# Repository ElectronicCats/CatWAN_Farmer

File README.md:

# CatWAN Farmer by Electronic Cats

CatWAN Farmer, a grower's water saving project

Monitoring soil moisture at different depths to determine when to irrigate, and - more importantly - how much water is needed. Save 25%!

## Main characteristics

- Provide low cost, easy to build, and rugged components for optimizing agricultural irrigation.
- DIY calibrated gypsum soil moisture sensors (Watermark SS200 is also supported).
- Hand held sensor reader (soil moisture, soil/water salinity, water pressure).
- Solar powered remote sensor platform.
- 4 electrically separated inputs for soil moisture sensors.
- LoRa module for long range (6 miles).
- temperature/humidity sensors.
- Solar battery charger.
- Real time clock for sleep mode power saving and precise irrigation timing.
- Gateway to connect multiple LoRa end nodes to the Internet.
- Supports packet mode LoRa® (package mode) or LoRaWAN ™ Class A, B and C.
- Compatible with Beelan, The Things Network and other LoRaWAN networks.
- Easy reprogramming compatible with Arduino and Circuit Python.

## Specifications

- 32-bit ARM Cortex-M0+ processor with 256KB flash, 32KB SRAM, and an operating speed of up to 48MHz. 
- Connectivity: USB 2.1.
- Vin: 4.2V-6.0V for charger - otherwise 3.5V-6.0V
- VBATT: 3.7V Lipo
- VCC: 600mA @3.3V
- Receiver Sensitivity: down to -146 dBm.
- TX Power: adjustable up to +18.5 dBm.
- Range: up to 15 km coverage in suburban and up to 5 km coverage.
- Watermark SS200 soil water tension sensor (4 x).
- Capacitive (FDR) volumetric soil moisture sensors (3x).
- Temperature and humidity.
- Compatible LoRa 915 and 868 Mhz.

## LICENSE

Hardware released under an CERN Open Hardware Licence v1.2. See the LICENSE_HARDWARE file for more information.

Designed by Electronic Cats.

Electronic Cats is a registered trademark, please do not use if you sell these PCBs.

Electronic Cats invests time and resources providing this open source design, please support Electronic Cats and open-source hardware by purchasing products from Electronic Cats!

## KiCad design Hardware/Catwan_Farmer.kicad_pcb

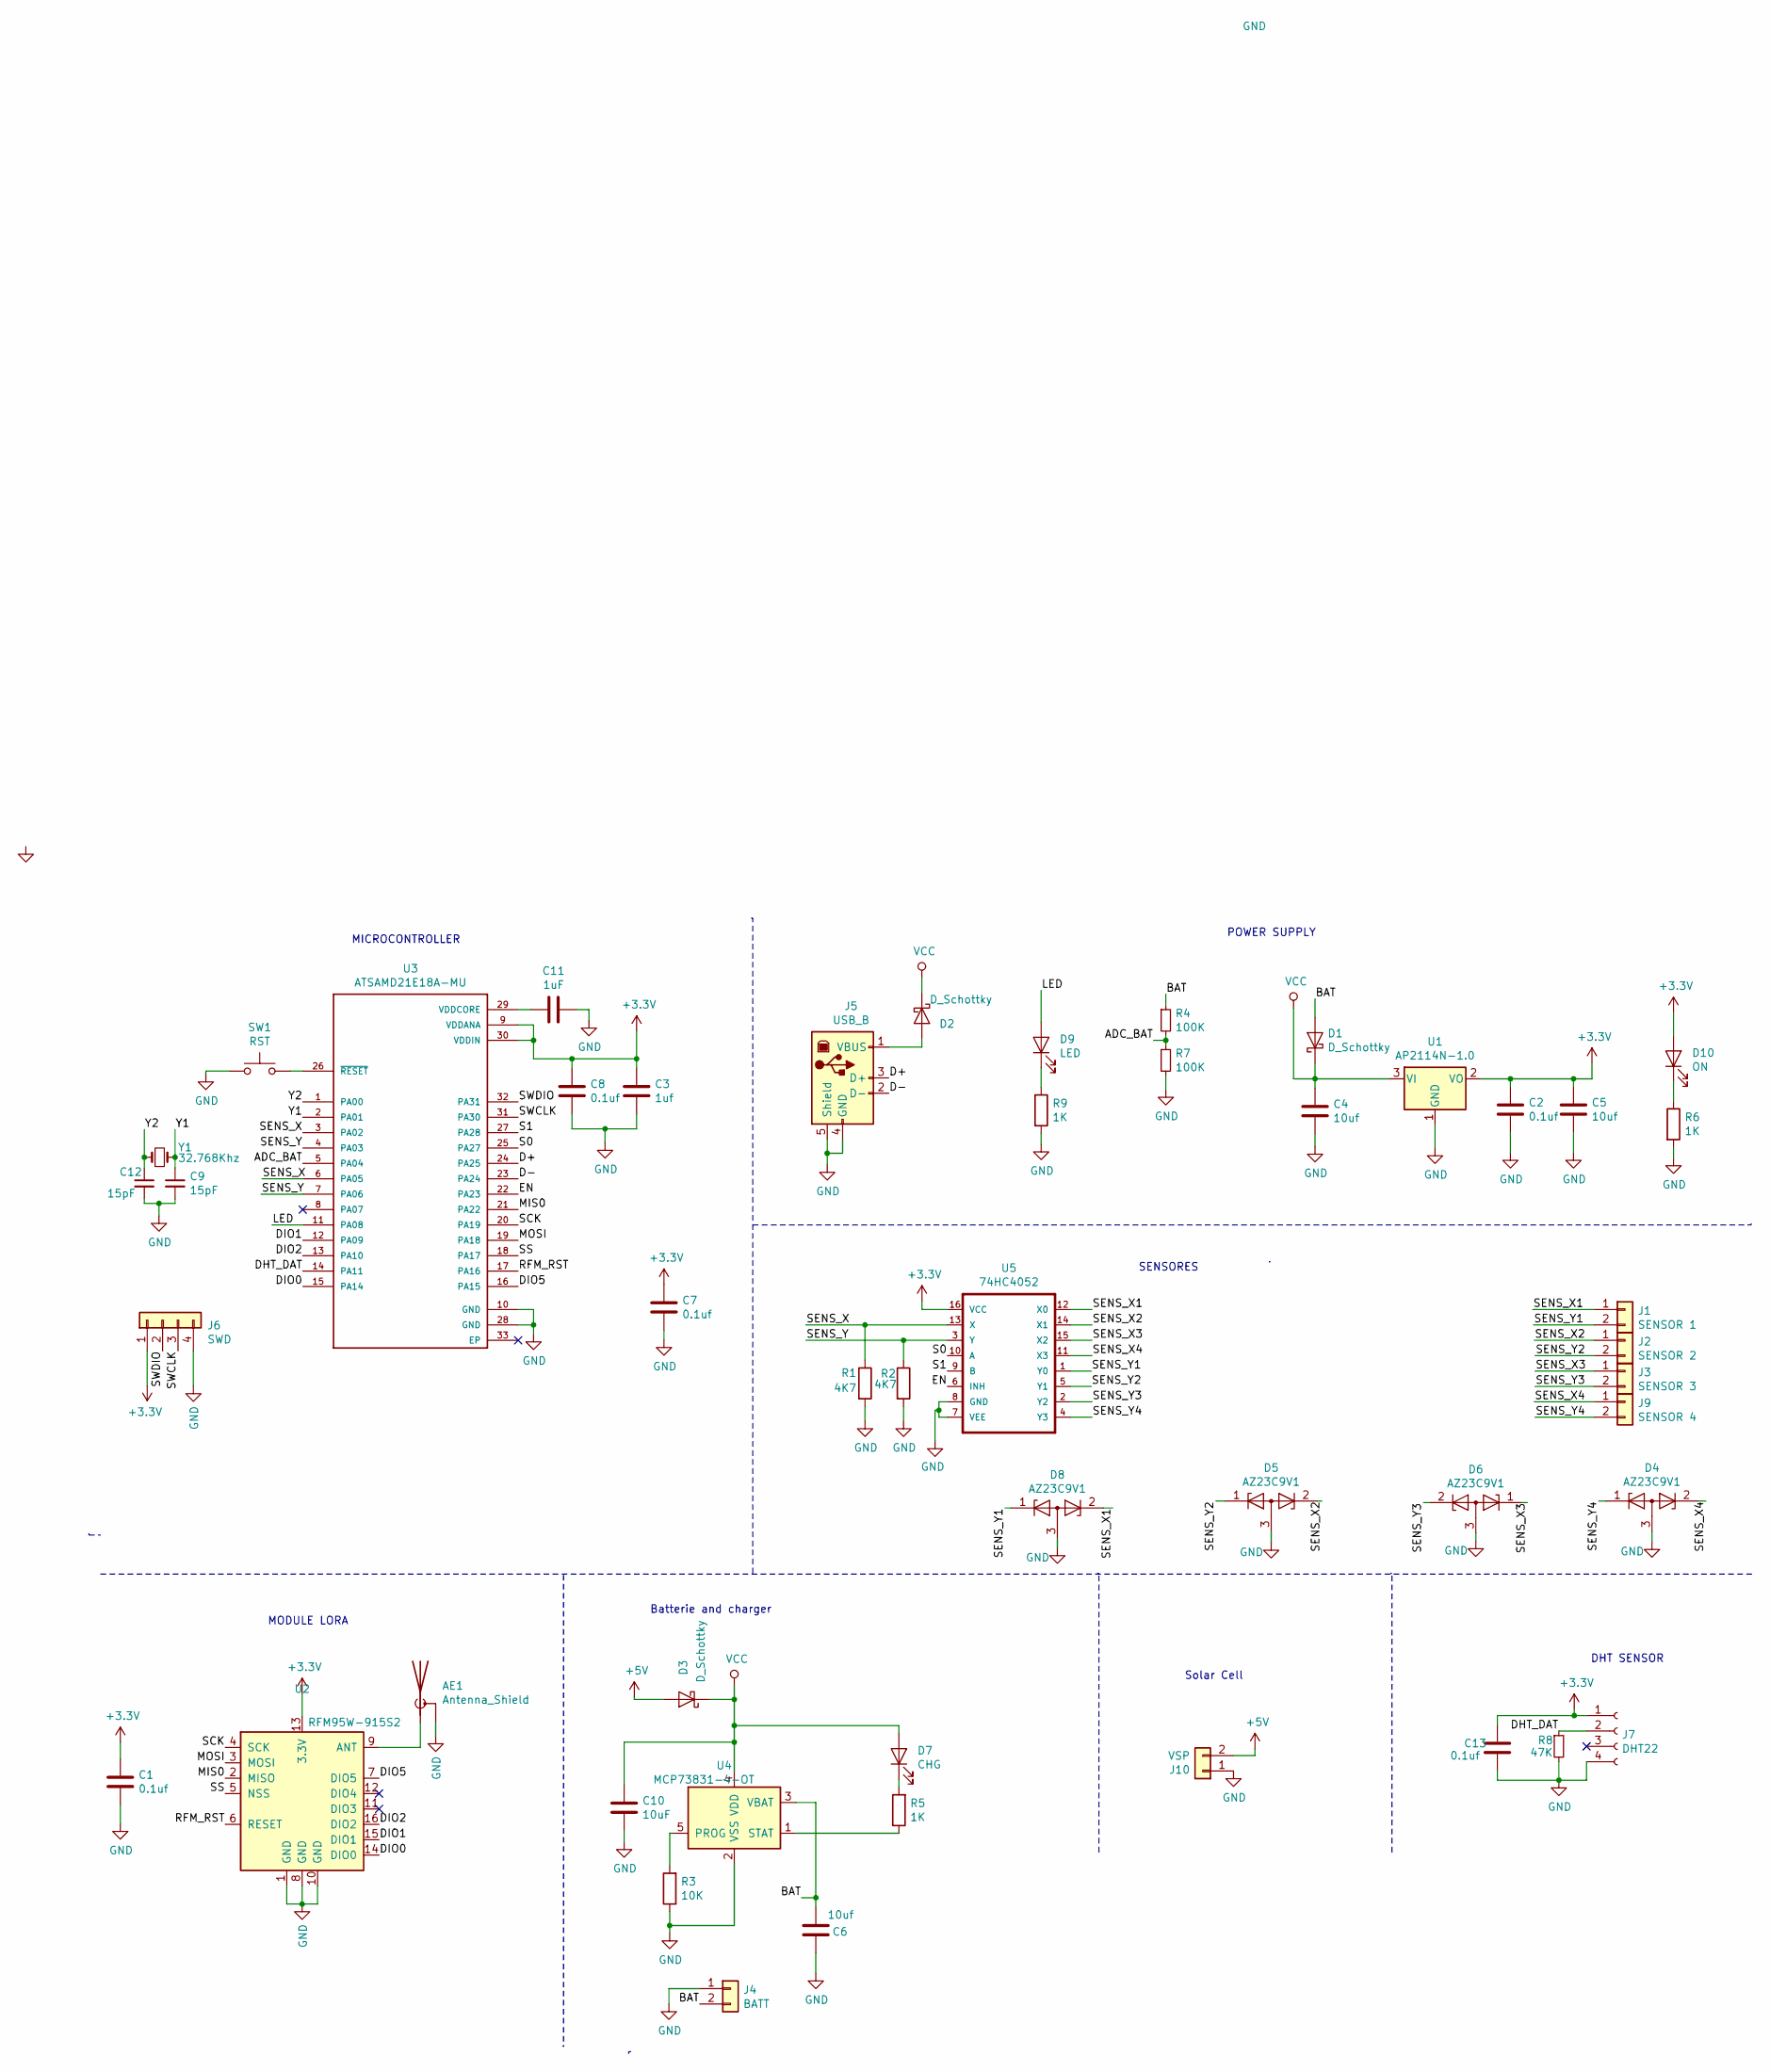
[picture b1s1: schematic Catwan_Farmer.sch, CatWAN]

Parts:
AE1: Antenna_Shield; AMPHENOL_901-144
C1, C2, C7, C8, C13: 0.1uf; C_0805_2012Metric_Pad1.15x1.40mm_HandSolder
C3: 1uf; C_0805_2012Metric_Pad1.15x1.40mm_HandSolder
C4, C5, C6: 10uf; C_0805_2012Metric_Pad1.15x1.40mm_HandSolder
C9, C12: 15pF; C_0805_2012Metric_Pad1.15x1.40mm_HandSolder
C10: 10uF; C_0805_2012Metric_Pad1.15x1.40mm_HandSolder
C11: 1uF; C_0805_2012Metric_Pad1.15x1.40mm_HandSolder
D1, D2, D3: D_Schottky; D_SOD-123
D4, D5, D6, D8: AZ23C9V1; SOT-23
D7: CHG; LED_0805_2012Metric_Pad1.15x1.40mm_HandSolder
D9: LED; LED_0805_2012Metric_Pad1.15x1.40mm_HandSolder
D10: ON; LED_0805_2012Metric_Pad1.15x1.40mm_HandSolder
J1: SENSOR 1; TerminalBlock_Phoenix_PT-1,5-2-3.5-H_1x02_P3.50mm_Horizontal
J2: SENSOR 2; TerminalBlock_Phoenix_PT-1,5-2-3.5-H_1x02_P3.50mm_Horizontal
J3: SENSOR 3; TerminalBlock_Phoenix_PT-1,5-2-3.5-H_1x02_P3.50mm_Horizontal
J4: BATT; TerminalBlock_Phoenix_PT-1,5-2-3.5-H_1x02_P3.50mm_Horizontal
J5: USB_B; U254051N4BH806
J6: SWD; PinHeader_1x04_P2.54mm_Vertical
J7: DHT22; PinHeader_1x04_P2.54mm_Vertical
J9: SENSOR 4; TerminalBlock_Phoenix_PT-1,5-2-3.5-H_1x02_P3.50mm_Horizontal
J10: VSP; TerminalBlock_Phoenix_PT-1,5-2-3.5-H_1x02_P3.50mm_Horizontal
R1, R2: 4K7; R_0805_2012Metric_Pad1.15x1.40mm_HandSolder
R3: 10K; R_0805_2012Metric_Pad1.15x1.40mm_HandSolder
R4, R7: 100K; R_0805_2012Metric_Pad1.15x1.40mm_HandSolder
R5, R6, R9: 1K; R_0805_2012Metric_Pad1.15x1.40mm_HandSolder
R8: 47K; R_0805_2012Metric_Pad1.15x1.40mm_HandSolder
SW1: RST; SW_SPST_SKQG_WithStem
U1: AP2114N-1.0; SOT-223-3_TabPin2
U2: RFM95W-915S2; HOPERF_RFM9XW_SMD
U3: ATSAMD21E18A-MU; TQFP-32_7x7mm_P0.8mm
U4: MCP73831-4-OT; SOT-23-5
U5: 74HC4052; SOIC-16_3.9x9.9mm_P1.27mm
Y1: 32.768Khz; Crystal_SMD_MicroCrystal_CC7V-T1A-2Pin_3.2x1.5mm_HandSolder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

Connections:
+3V3: C1.1, C2.1, C3.1, C5.1, C7.1, C8.1, C13.1, D10.2 (A), J6.1, J7.1, U1.2 (VO), U2.13 (3.3V), U3.9 (VDDANA), U3.30 (VDDIN), U5.16 (VCC)
+5V: D3.2 (A), J10.2
/ADC_BAT: R4.2, R7.1, U3.5 (PA04)
/BAT: C6.2, D1.2 (A), J4.2, R4.1, U4.3 (VBAT)
/D+: J5.3 (D+), U3.24 (PA25)
/D-: J5.2 (D-), U3.23 (PA24)
/DHT_DAT: J7.2, R8.1, U3.14 (PA11)
/DIO0: U2.14 (DIO0), U3.15 (PA14)
/DIO1: U2.15 (DIO1), U3.12 (PA09)
/DIO2: U2.16 (DIO2), U3.13 (PA10)
/DIO5: U2.7 (DIO5), U3.16 (PA15)
/EN: U3.22 (PA23), U5.6 (INH)
/LED: D9.2 (A), U3.11 (PA08)
/MIS0: U2.2 (MISO), U3.21 (PA22)
/MOSI: U2.3 (MOSI), U3.19 (PA18)
/RFM_RST: U2.6 (RESET), U3.17 (PA16)
/S0: U3.25 (PA27), U5.10 (A)
/S1: U3.27 (PA28), U5.9 (B)
/SCK: U2.4 (SCK), U3.20 (PA19)
/SENS_X: R1.1, U3.3 (PA02), U3.6 (PA05), U5.13 (X)
/SENS_X1: D8.2 (K), J1.1, U5.12 (X0)
/SENS_X2: D5.2 (K), J2.1, U5.14 (X1)
/SENS_X3: D6.1 (K), J3.1, U5.15 (X2)
/SENS_X4: D4.2 (K), J9.1, U5.11 (X3)
/SENS_Y: R2.1, U3.4 (PA03), U3.7 (PA06), U5.3 (Y)
/SENS_Y1: D8.1 (K), J1.2, U5.1 (Y0)
/SENS_Y2: D5.1 (K), J2.2, U5.5 (Y1)
/SENS_Y3: D6.2 (K), J3.2, U5.2 (Y2)
/SENS_Y4: D4.1 (K), J9.2, U5.4 (Y3)
/SS: U2.5 (NSS), U3.18 (PA17)
/SWCLK: J6.3, U3.31 (PA30)
/SWDIO: J6.2, U3.32 (PA31)
/Y1: C9.1, U3.2 (PA01), Y1.2
/Y2: C12.1, U3.1 (PA00), Y1.1
GND: AE1.2 (Shield), C1.2, C2.2, C3.2, C4.2, C5.2, C6.1, C7.2, C8.2, C9.2, C10.2, C11.1, C12.2, C13.2, D4.3 (A), D5.3 (A), D6.3 (A), D8.3 (A), J4.1, J5.4 (GND), J5.5 (Shield), J6.4, J7.4, J10.1, R1.2, R2.2, R3.1, R6.2, R7.2, R8.2, R9.2, SW1.1, U1.1 (GND), U2.1 (GND), U2.8 (GND), U2.10 (GND), U3.10 (GND), U3.28 (GND), U4.2 (VSS), U5.7 (VEE), U5.8 (GND)
unnamed: AE1.1 (A), U2.9 (ANT)
unnamed: C11.2, U3.29 (VDDCORE)
unnamed: D2.2 (A), J5.1 (VBUS)
unnamed: D7.1 (K), R5.2
unnamed: D9.1 (K), R9.1
unnamed: D10.1 (K), R6.1
unnamed: R3.2, U4.5 (PROG)
unnamed: R5.1, U4.1 (STAT)
unnamed: SW1.2, U3.26 (~RESET~)
VCC: C4.1, C10.1, D1.1 (K), D2.1 (K), D3.1 (K), D7.2 (A), U1.3 (VI), U4.4 (VDD)

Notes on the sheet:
MICROCONTROLLER
POWER SUPPLY
MODULE LORA
SENSORES
Solar Cell
DHT SENSOR
Batterie and charger

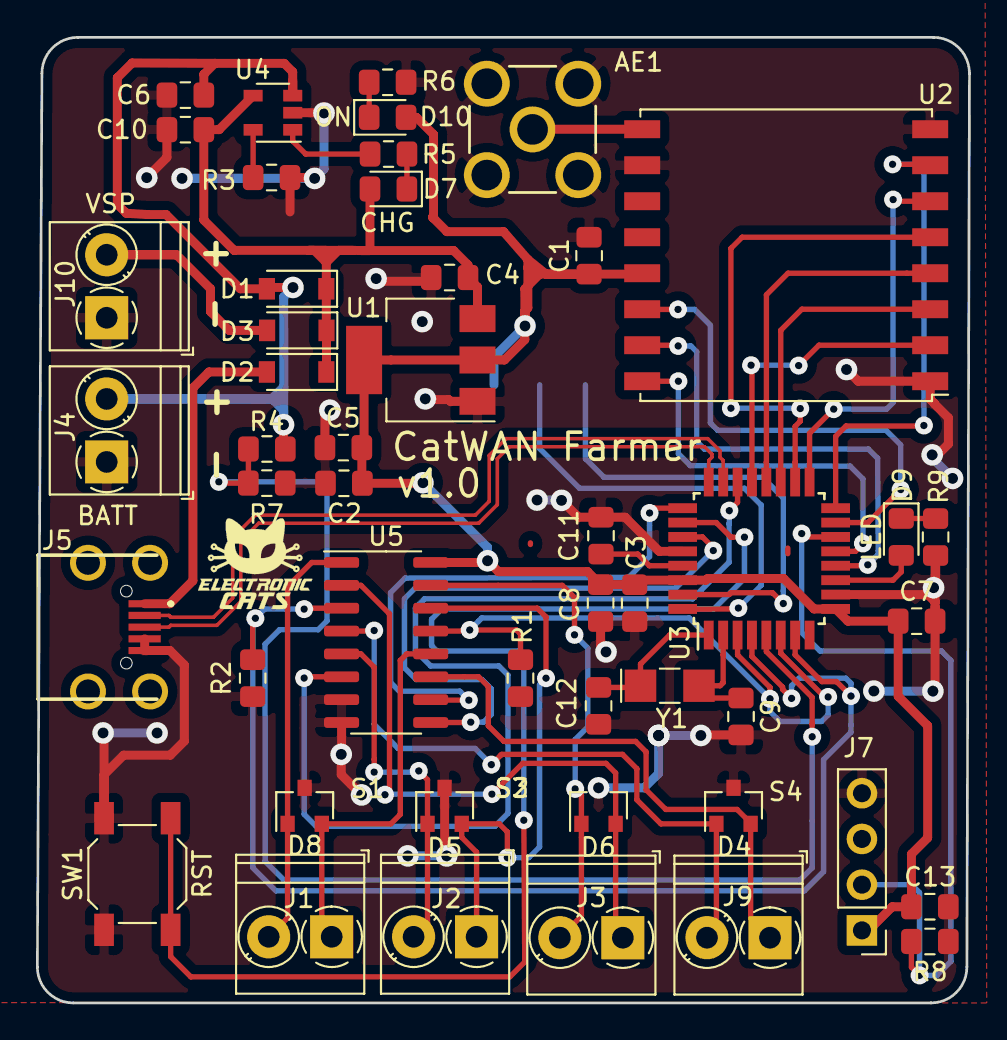
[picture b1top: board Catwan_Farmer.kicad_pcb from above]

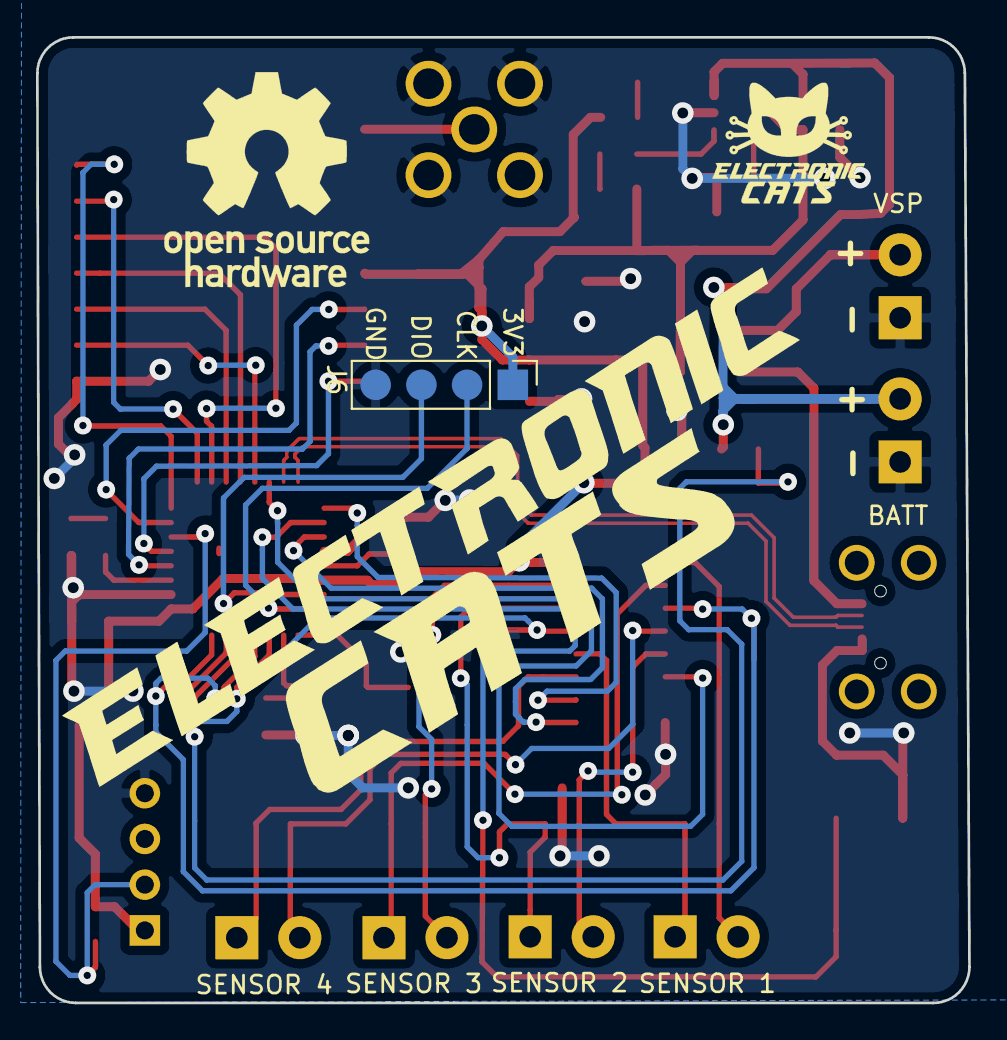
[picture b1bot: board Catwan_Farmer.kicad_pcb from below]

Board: 2 copper layers, 51.8 x 53.6 mm, 50 parts (2 on the bottom side), 45 nets.

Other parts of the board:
svg2mod: electronic; titule_electronic_med

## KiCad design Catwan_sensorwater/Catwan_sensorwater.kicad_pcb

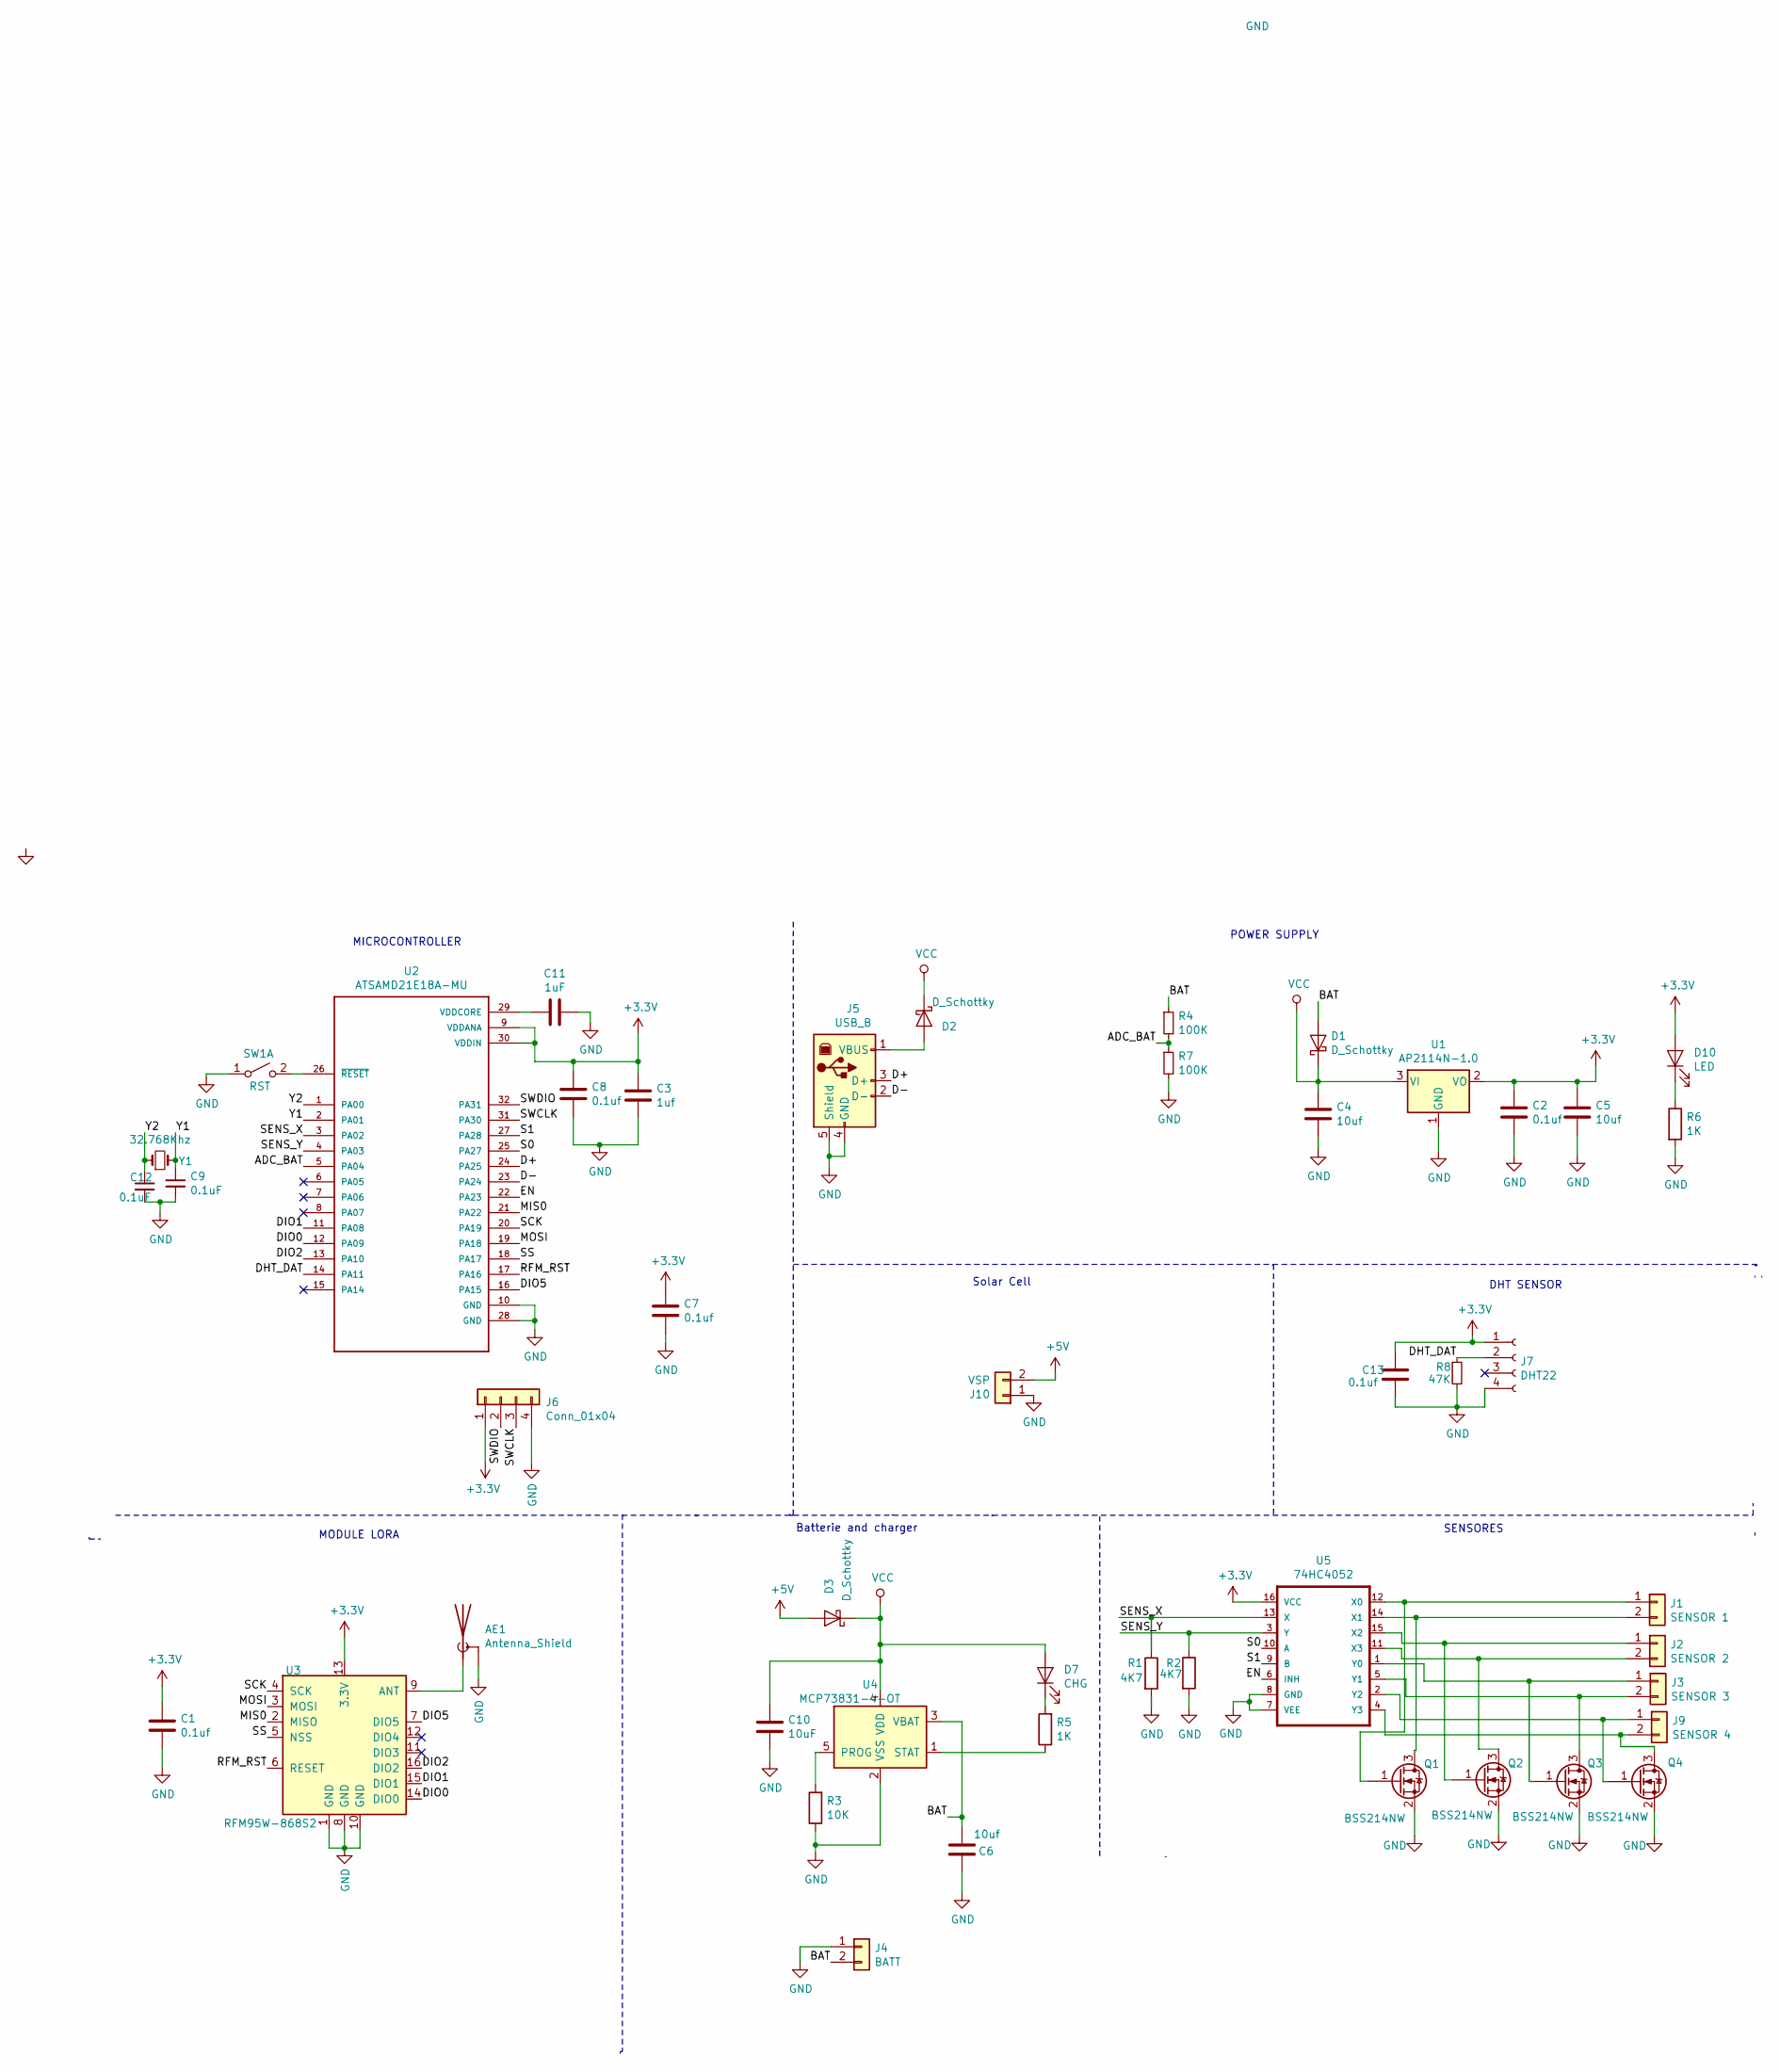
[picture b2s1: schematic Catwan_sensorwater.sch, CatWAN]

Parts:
AE1: Antenna_Shield; AMPHENOL_901-144
C1, C2, C7, C8, C13: 0.1uf; C_0805_2012Metric_Pad1.15x1.40mm_HandSolder
C3: 1uf; C_0805_2012Metric_Pad1.15x1.40mm_HandSolder
C4, C5, C6: 10uf; C_0805_2012Metric_Pad1.15x1.40mm_HandSolder
C9, C12: 0.1uF; C_0805_2012Metric_Pad1.15x1.40mm_HandSolder
C10: 10uF; C_0805_2012Metric_Pad1.15x1.40mm_HandSolder
C11: 1uF; C_0805_2012Metric_Pad1.15x1.40mm_HandSolder
D1, D2, D3: D_Schottky; D_SOD-123
D7: CHG; LED_0805_2012Metric_Pad1.15x1.40mm_HandSolder
D10: LED; LED_0805_2012Metric_Pad1.15x1.40mm_HandSolder
J1: SENSOR 1; TerminalBlock_Phoenix_PT-1,5-2-3.5-H_1x02_P3.50mm_Horizontal
J2: SENSOR 2; TerminalBlock_Phoenix_PT-1,5-2-3.5-H_1x02_P3.50mm_Horizontal
J3: SENSOR 3; TerminalBlock_Phoenix_PT-1,5-2-3.5-H_1x02_P3.50mm_Horizontal
J4: BATT; TerminalBlock_Phoenix_PT-1,5-2-3.5-H_1x02_P3.50mm_Horizontal
J5: USB_B; USB_Micro-B_Wuerth_629105150521
J6: Conn_01x04; PinHeader_1x04_P2.54mm_Vertical
J7: DHT22; PinHeader_1x04_P2.54mm_Vertical
J9: SENSOR 4; TerminalBlock_Phoenix_PT-1,5-2-3.5-H_1x02_P3.50mm_Horizontal
J10: VSP; TerminalBlock_Phoenix_PT-1,5-2-3.5-H_1x02_P3.50mm_Horizontal
Q1, Q2, Q3, Q4: BSS214NW; SOT-23
R1, R2: 4K7; R_0805_2012Metric_Pad1.15x1.40mm_HandSolder
R3: 10K; R_0805_2012Metric_Pad1.15x1.40mm_HandSolder
R4, R7: 100K; R_0805_2012Metric_Pad1.15x1.40mm_HandSolder
R5, R6: 1K; R_0805_2012Metric_Pad1.15x1.40mm_HandSolder
R8: 47K; R_0805_2012Metric_Pad1.15x1.40mm_HandSolder
SW1: RST; SW_SPST_TL3342
U1: AP2114N-1.0; SOT-223-3_TabPin2
U2: ATSAMD21E18A-MU; TQFP-32_7x7mm_P0.8mm
U3: RFM95W-868S2; RFM95W
U4: MCP73831-4-OT; SOT-23-5
U5: 74HC4052; SOIC-16_3.9x9.9mm_P1.27mm
Y1: 32.768Khz; Crystal_AT310_d3.0mm_l10.0mm_Vertical

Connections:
+3V3: C1.1, C2.1, C3.1, C5.1, C7.1, C8.1, C13.1, D10.2 (A), J6.1, J7.1, U1.2 (VO), U2.9 (VDDANA), U2.30 (VDDIN), U3.13 (3.3V), U5.16 (VCC)
+5V: D3.2 (A), J10.2
/ADC_BAT: R4.2, R7.1, U2.5 (PA04)
/BAT: C6.2, D1.2 (A), J4.2, R4.1, U4.3 (VBAT)
/D+: J5.3 (D+), U2.24 (PA25)
/D-: J5.2 (D-), U2.23 (PA24)
/DHT_DAT: J7.2, R8.1, U2.14 (PA11)
/DIO2: U2.13 (PA10), U3.16 (DIO2)
/DIO5: U2.16 (PA15), U3.7 (DIO5)
/EN: U2.22 (PA23), U5.6 (INH)
/MIS0: U2.21 (PA22), U3.2 (MISO)
/MOSI: U2.19 (PA18), U3.3 (MOSI)
/RFM_RST: U2.17 (PA16), U3.6 (RESET)
/S0: U2.25 (PA27), U5.10 (A)
/S1: U2.27 (PA28), U5.9 (B)
/SCK: U2.20 (PA19), U3.4 (SCK)
/SENS_X: R1.1, U2.3 (PA02), U5.13 (X)
/SENS_Y: R2.1, U2.4 (PA03), U5.3 (Y)
/SS: U2.18 (PA17), U3.5 (NSS)
/SWCLK: J6.3, U2.31 (PA30)
/SWDIO: J6.2, U2.32 (PA31)
/Y1: C9.1, U2.2 (PA01), Y1.2
/Y2: C12.1, U2.1 (PA00), Y1.1
GND: AE1.2 (Shield), C1.2, C2.2, C3.2, C4.2, C5.2, C6.1, C7.2, C8.2, C9.2, C10.2, C11.1, C12.2, C13.2, J4.1, J5.4 (GND), J5.5 (Shield), J6.4, J7.4, J10.1, Q1.2 (S), Q2.2 (S), Q3.2 (S), Q4.2 (S), R1.2, R2.2, R3.1, R6.2, R7.2, R8.2, SW1.1 (A), U1.1 (GND), U2.10 (GND), U2.28 (GND), U3.1 (GND), U3.8 (GND), U3.10 (GND), U4.2 (VSS), U5.7 (VEE), U5.8 (GND)
unnamed: AE1.1 (A), U3.9 (ANT)
unnamed: C11.2, U2.29 (VDDCORE)
unnamed: D2.2 (A), J5.1 (VBUS)
unnamed: D7.1 (K), R5.2
unnamed: D10.1 (K), R6.1
unnamed: J1.1, Q1.1 (G), U5.12 (X0)
unnamed: J1.2, Q1.3 (D), U5.14 (X1)
unnamed: J2.1, Q2.1 (G), U5.15 (X2)
unnamed: J2.2, Q2.3 (D), U5.11 (X3)
unnamed: J3.1, Q3.1 (G), U5.1 (Y0)
unnamed: J3.2, Q3.3 (D), U5.5 (Y1)
unnamed: J9.1, Q4.1 (G), U5.2 (Y2)
unnamed: J9.2, Q4.3 (D), U5.4 (Y3)
unnamed: R3.2, U4.5 (PROG)
unnamed: R5.1, U4.1 (STAT)
unnamed: SW1.2 (B), U2.26 (~RESET~)
VCC: C4.1, C10.1, D1.1 (K), D2.1 (K), D3.1 (K), D7.2 (A), U1.3 (VI), U4.4 (VDD)

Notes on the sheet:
MICROCONTROLLER
POWER SUPPLY
MODULE LORA
SENSORES
Solar Cell
DHT SENSOR
Batterie and charger

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
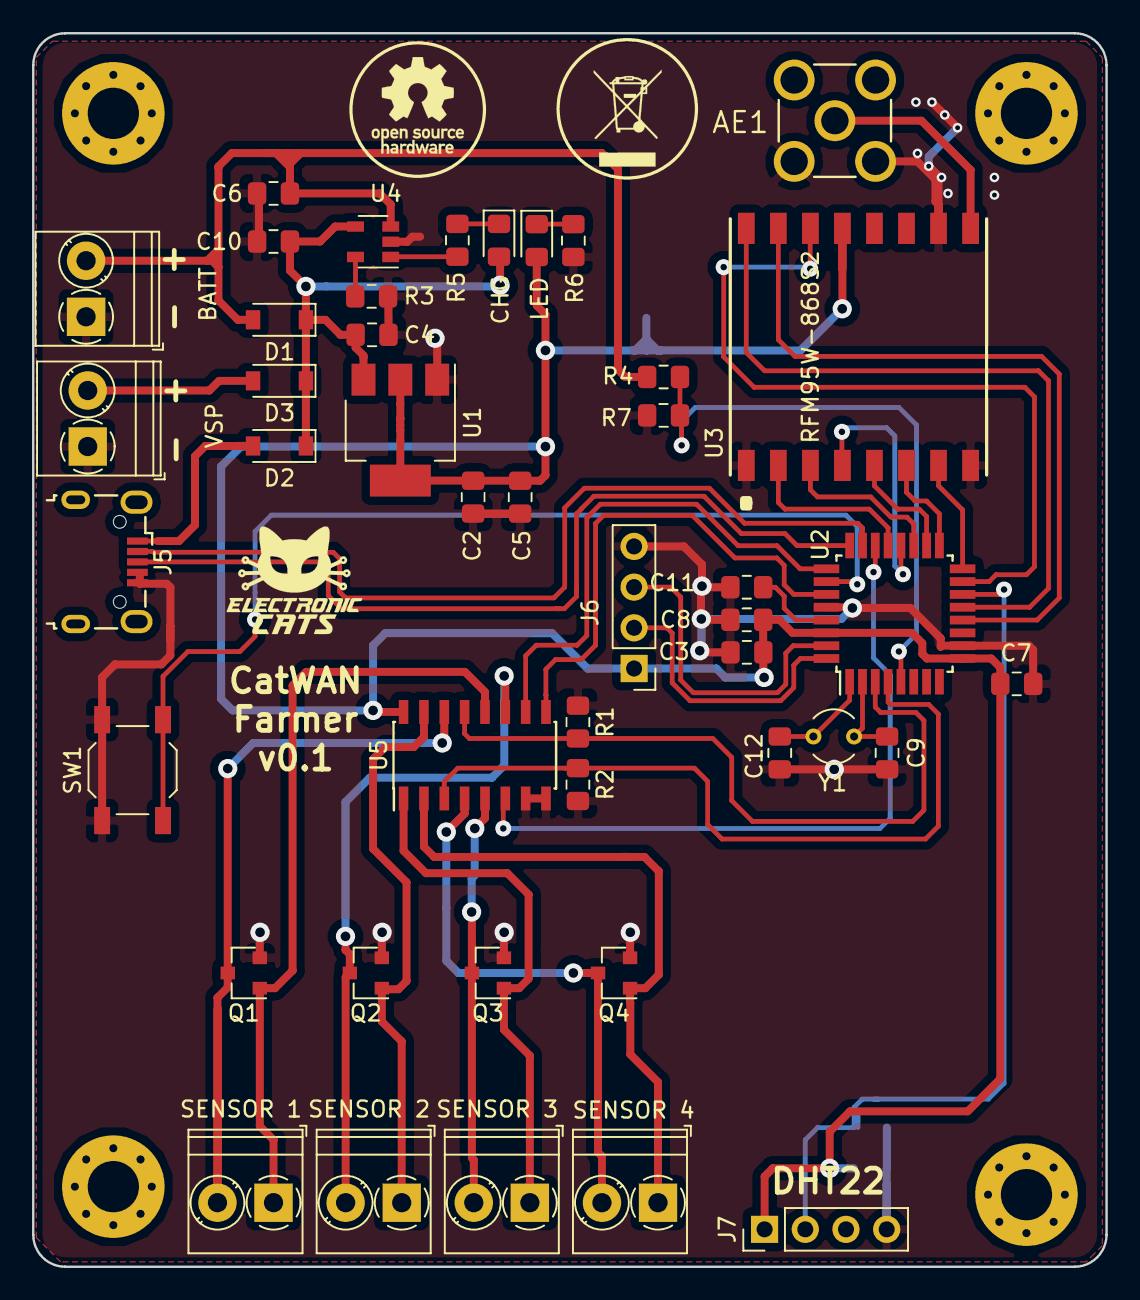
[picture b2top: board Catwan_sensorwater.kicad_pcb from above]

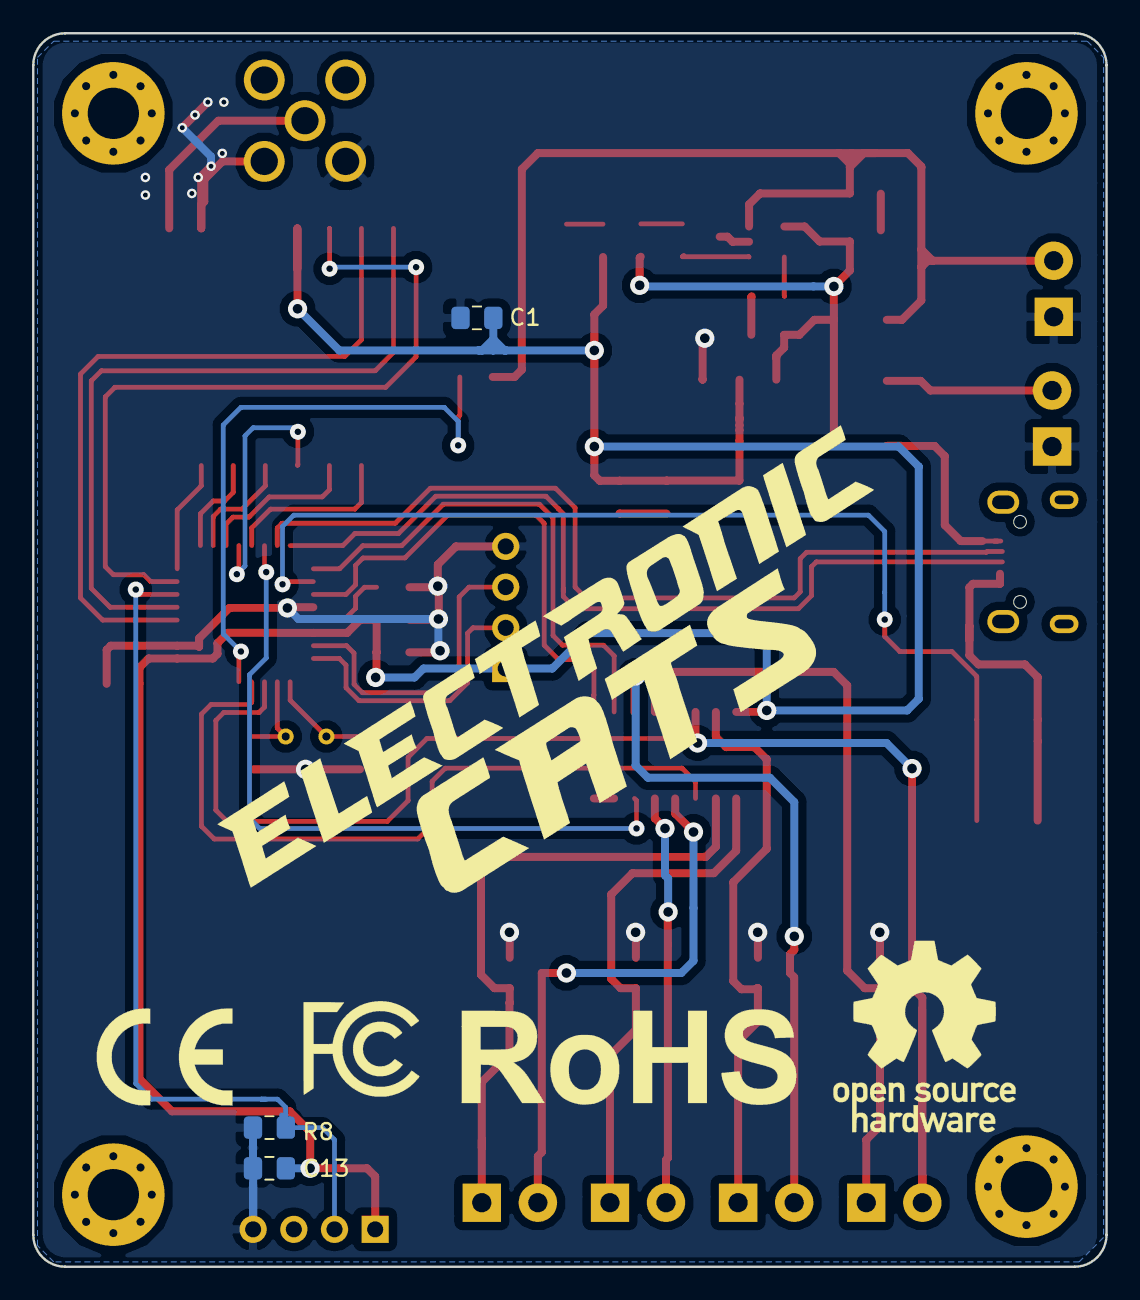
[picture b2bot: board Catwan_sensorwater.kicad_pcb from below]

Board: 2 copper layers, 67.0 x 77.0 mm, 48 parts (4 on the bottom side), 43 nets.

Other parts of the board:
svg2mod: electronic; titule_electronic_med

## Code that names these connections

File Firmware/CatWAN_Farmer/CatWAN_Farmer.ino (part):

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// Setting up format for reading 4 soil sensors
#define NUM_READS 10   // Number of sensor reads for filtering

#define SENS_X 5
#define SENS_Y 6
#define ENABLE 23
#define S0 27
#define S1 28
#define ADC_BAT A2
#define DHTPIN 11
#define DHTTYPE DHT22

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const sRFM_pins RFM_pins = {
  .CS = 20,
  .RST = 9,
  .DIO0 = 0,
  .DIO1 = 1,
  .DIO2 = 2,
  .DIO5 = 15,
};
*/

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  // setting up the sensor interface
  // initialize digital pins D5, D6 as an high impedance input.
  // Pin 5,6 are f846r driving the soil moisture sensor
  pinMode(SENS_X, INPUT); // SENS_X
  pinMode(SENS_Y, INPUT); // SENS_Y
  // Pin 7 is for enabling Mux switches
  pinMode(ENABLE, OUTPUT); //ENABLE
  // Pin 8,9 are for selecting sensor 1-4
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  for (i = 0; i < NUM_READS; i++)
  {

    pinMode(SENS_X, OUTPUT);
    digitalWrite(SENS_X, HIGH);
    delayMicroseconds(25);
    sensorVoltage = analogRead(A1);   // read the sensor voltage
    supplyVoltage = analogRead(A0);   // read the supply voltage
    delayMicroseconds(25);
    digitalWrite(SENS_X, LOW);
    pinMode(SENS_X, INPUT);
    delay(100);
    long resistance = (knownResistor * (supplyVoltage - sensorVoltage ) / sensorVoltage) - zeroCalibration ;
    addReading(resistance);
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#endif
    delay(1);

    pinMode(SENS_Y, OUTPUT);
    digitalWrite(SENS_Y, LOW);
    digitalWrite(SENS_Y, HIGH);
    delayMicroseconds(25);
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    supplyVoltage = analogRead(A1);   // read the supply voltage
    delayMicroseconds(25);
    digitalWrite(SENS_Y, LOW);
    pinMode(SENS_Y, INPUT);

    resistance = (knownResistor * (supplyVoltage - sensorVoltage ) / sensorVoltage) - zeroCalibration ;
    delay(100);
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
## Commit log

2018-09-24 Project_kiCad
2018-09-26 Regulador
    3.3V
2018-09-29 Agregue ATSAMD Y LORA
2018-10-01 Read sensor humidity arduino 1
2018-10-02 SENSORES, MULTIPLEXOR
2018-10-03 Multiplexor casi listo.
2018-10-03 asignación huellas
2018-10-04 Read voltaje divisor SAMD21
2018-10-04 Read MUX A0 A1
2018-10-09 batería agregada.
2018-10-10 huellas
    Cambios
2018-10-25 add s0 s1 ans enable in multiplexer
2018-10-25 Edit ATSAMD separate pin 10 and 28 an no connected
2018-10-25 Capacitor VCC SAMD
2018-10-26 Edit connections
2018-10-26 Adjust of regulator
2018-10-30 Connector ID
2018-10-30 Fix
    Serial SWD
2018-10-31 Pin modificado
    separados
2018-10-31 Footprints
2018-10-31 Auto stash before merge of "master" and "origin/master"
    Change zener for MOSFET
2018-10-31 add 3.3V to mux
2018-10-31 Annotate no. MOSFET
2018-10-31 ADD HUMIDITY SENSOR
2018-11-01 Add 4 sensor
2018-11-07 snapshot v0.3
    Update source to VCC, and check ERC
2018-11-07 remove resistence for DHT22
2018-11-12 Capacitor .1
2018-11-13 Changes connections and error
2018-11-13 Connections and error
2018-11-13 Finished schematic
2018-11-13 schematic modified
2018-11-13 Netlist
2018-11-13 Mover carpeta software
2018-11-13 change pines j6
2018-11-13 Change j7
2018-11-13 Inicio PCB
2018-11-16 acomodo
2018-11-17 Acomodo segunda parte
2018-11-20 Acomodo componentes
2018-11-21 Rooteo
2018-11-22 Segunda parte
2018-11-22 distribution devices
2018-11-22 Change diodes
2018-11-22 clear schematic
2018-11-23 change pcb
2018-11-23 components back to the front
2018-11-23 diode shottkie and regulator packege
2018-11-24 new accommodation
2018-11-24 Corrections
2018-11-26 change label batt
2018-11-26 source
2018-11-26 pin read x and y
2019-01-15 add DHT
2019-01-19 Rooteo new accommodation
2019-01-22 Rooteo GND
2019-01-22 test mux
2019-01-23 Changes rooteo
2019-01-24 Microcontroller GND
2019-01-25 Changes GND
2019-01-25 Check rooteo
2019-01-25 Track correction
2019-01-28 Add diode and capacitor, food print assignment and list of networks
2019-01-28 Adapter capacitor and diode
2019-01-29 Change food print microcontroller
2019-01-29 Netlist microcontroller routeo
2019-01-29 Routeo changes with new footprint
2019-01-29 Add diodes in vsp, remove capacitor and 10k resistance
2019-01-30 Add foodprint D3
2019-02-05 Netlist D3
2019-02-08 changes foodprint diode
2019-02-08 Add D3 PCB
2019-02-09 New routeo
2019-02-11 remove serial port
2019-02-12 new netlist and accommodation
2019-02-19 Change name CatWAN Farmer
2019-02-20 Add logo and autors
2019-02-20 add RTC and ADC Battery
2019-02-21 New metlist add the components to the pcb and start of routeo
2019-02-21 move components
2019-02-21 Routeo bss21
2019-02-22 Routeo and ground plane
2019-02-22 add circuit DHT2
2019-02-22 DHT22 Schematic
2019-02-22 add m3
2019-02-22 margen
2019-02-22 logos
2019-02-23 v0.1beta
2019-02-23 Update component placement and pot
2019-02-23 change dio0 interrumption
2019-02-23 dio0 schematic
2019-02-25 Rename project
2019-02-25 Rename Folders
2019-02-25 Value Mosfet
2019-04-17 add LED and sens voltage
2019-04-17 add test
2019-05-25 change test
2019-05-27 change mosfet to zenner
2020-01-14 update led, switch and labels
2020-01-17 Change sens_y analog pin
2020-01-17 No conect pin 8
2020-03-17 Fix multiplexor
2020-03-24 Update simbols cache
2020-03-24 division of schematic
2020-03-24 Update footprints
2020-03-24 gnd and blink
2020-03-24 fix c8 and c3
2020-03-25 add footprint crystal and value c8 and c3, fix footprint u3, u2 usb
2020-03-27 Initial pcb
2020-04-23 End place components
2020-05-14 Measure pcb
2020-05-14 edge cuts
2020-05-14 gnd plane
2020-05-14 7HC40 and Diodes
2020-05-15 routeo samd
2020-05-15 RFM95
2020-05-18 New routeo pcb
2020-05-20 Measurements
2020-06-06 New size pcb
2020-06-06 Routeo new size pcb
2020-06-11 Fix tracks samd
2020-06-11 Change tracks D- D+
2020-06-17 Manf#
2020-07-07 Update pinout
2020-07-07 fix change index for indice
2020-07-07 fin index ok
2020-07-08 fix error pinout sensors
2020-07-17 New netlist
2020-07-18 Change conn sensors
2020-07-21 Change DI0 and CLK
2020-07-21 Sensors
2020-07-23 fix DHT and swd change r1 and r2
2020-07-29 sensors Arduino
2020-08-03 CatWan Resistance
2020-08-03 sensors farmer
2020-08-04 --Test
2020-08-05 Sensor+RTC
2020-08-06 auto format
2020-08-06 Add defines for debug and selecte sensor enable
2020-08-06 auto format firmware farmer
2020-08-06 remove example
2020-08-06 rename examples
2020-08-06 remove Serial USB double
2020-08-06 Update soilsensors
2020-08-06 Update measureSensor
2020-08-07 Mode sleep
2020-08-10 WM_Resistance and sleep 10s
2020-08-19 add keys
2020-08-19 correction adc
